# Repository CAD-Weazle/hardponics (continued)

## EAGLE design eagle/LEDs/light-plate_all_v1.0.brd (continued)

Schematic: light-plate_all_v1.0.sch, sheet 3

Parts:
C30D, C31D, C32D: 10U/50V; CAP0603
C30P, C31P, C32P: 1U; CAP0603
D30, D31, D32: MBR0530; DIODE_SOD123
H5, H6, H7, H8, H9, H10: HOLE_PTH_1.0MM
L30, L31, L32: SDR0604-101KL; L_SDR0604
LD30DR, LD30DR1, LD30DR2, LD30DR3, LD30DR4, LD30DR5, LD30DR6, LD30DR7, LD30DR8, LD30DR9, LD30DR10, LD30DR11, LD30DR12, LD30DR13, LD30DR14, LD30DR15, LD30DR16, LD30DR17, LD30DR18, LD30DR19, LD30DR20, LD30DR21, LD30DR22, LD30DR23, LD30DR24, LD30DR25, LD30DR26, LD30DR27, LD30DR28, LD30DR29, LD30DR30, LD30DR31, LD30DR32, LD30DR33, LD30DR34, LD30DR35, LD30DR36, LD30DR37, LD30DR38, LD30DR39, LD30DR40, LD30DR41, LD30DR42, LD30DR43, LD30DR44, LD30DR45, LD30DR46, LD30DR47, LD30DR48, LD30DR49, LD30DR50, LD30DR51, LD30DR52, LD30DR53, LD30DR54, LD30DR55, LD30DR56, LD30DR57, LD30DR58, LD30DR59, LD30DR60, LD30DR61, LD30DR62, LD30DR63, LD30DR64, LD30DR65, LD30DR66, LD30DR67, LD30DR68, LD30DR69, LD30DR70, LD30DR71, LD30DR72, LD30DR73, LD30DR74, LD30DR75, LD30DR76, LD30DR77, LD30DR78, LD30DR79, LD30DR80, LD30DR81, LD30DR82, LD30DR83, LD30DR84, LD30DR85, LD30DR86, LD30DR87, LD30DR88, LD30DR89, LD30DR90, LD30DR91, LD30DR92, LD30DR93, LD30DR94, LD30DR95, LD30DR96, LD30DR97, LD30DR98: L1SP-DRD00035R0000; LED_SMD_SUNPLUS35_REVERSED
R30, R31, R32: 0R5; RES0603
R30P, R31P, R32P: 10K; RES0603
U30, U31, U32: AL8860; SOT23-5

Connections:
DRED_PWM0: R30P.1; also elsewhere on the board
DRED_PWM1: R31P.1; also elsewhere on the board
DRED_PWM2: R32P.1; also elsewhere on the board
GND: C30D.2, C30P.2, C31D.2, C31P.2, C32D.2, C32P.2, U30.2 (2.GND), U31.2 (2.GND), U32.2 (2.GND); also elsewhere on the board
unnamed: C30P.1, R30P.2, U30.3 (3.VSET)
unnamed: LD30DR.A (-), LD30DR1.C (+)
unnamed: LD30DR1.A (-), LD30DR2.C (+)
unnamed: LD30DR2.A (-), LD30DR3.C (+)
unnamed: LD30DR3.A (-), LD30DR4.C (+)
unnamed: LD30DR4.A (-), LD30DR5.C (+)
unnamed: LD30DR5.A (-), LD30DR6.C (+)
unnamed: LD30DR6.A (-), LD30DR7.C (+)
unnamed: LD30DR7.A (-), LD30DR8.C (+)
unnamed: LD30DR8.A (-), LD30DR9.C (+)
unnamed: LD30DR9.A (-), LD30DR10.C (+)
unnamed: LD30DR11.A (-), LD30DR12.C (+)
unnamed: LD30DR12.A (-), LD30DR13.C (+)
unnamed: LD30DR13.A (-), LD30DR14.C (+)
unnamed: LD30DR14.A (-), LD30DR15.C (+)
unnamed: LD30DR15.A (-), LD30DR16.C (+)
unnamed: LD30DR16.A (-), LD30DR17.C (+)
unnamed: LD30DR17.A (-), LD30DR18.C (+)
unnamed: LD30DR18.A (-), LD30DR19.C (+)
unnamed: LD30DR19.A (-), LD30DR20.C (+)
unnamed: LD30DR20.A (-), LD30DR21.C (+)
unnamed: LD30DR22.A (-), LD30DR23.C (+)
unnamed: LD30DR23.A (-), LD30DR24.C (+)
unnamed: LD30DR24.A (-), LD30DR25.C (+)
unnamed: LD30DR25.A (-), LD30DR26.C (+)
unnamed: LD30DR26.A (-), LD30DR27.C (+)
unnamed: LD30DR27.A (-), LD30DR28.C (+)
unnamed: LD30DR28.A (-), LD30DR29.C (+)
unnamed: LD30DR29.A (-), LD30DR30.C (+)
unnamed: LD30DR30.A (-), LD30DR31.C (+)
unnamed: LD30DR31.A (-), LD30DR32.C (+)
unnamed: LD30DR33.A (-), LD30DR34.C (+)
unnamed: LD30DR34.A (-), LD30DR35.C (+)
unnamed: LD30DR35.A (-), LD30DR36.C (+)
unnamed: LD30DR36.A (-), LD30DR37.C (+)
unnamed: LD30DR37.A (-), LD30DR38.C (+)
unnamed: LD30DR38.A (-), LD30DR39.C (+)
unnamed: LD30DR39.A (-), LD30DR40.C (+)
unnamed: LD30DR40.A (-), LD30DR41.C (+)
unnamed: LD30DR41.A (-), LD30DR42.C (+)
unnamed: LD30DR42.A (-), LD30DR43.C (+)
unnamed: LD30DR44.A (-), LD30DR45.C (+)
unnamed: LD30DR45.A (-), LD30DR46.C (+)
unnamed: LD30DR46.A (-), LD30DR47.C (+)
unnamed: LD30DR47.A (-), LD30DR48.C (+)
unnamed: LD30DR48.A (-), LD30DR49.C (+)
unnamed: LD30DR49.A (-), LD30DR50.C (+)
unnamed: LD30DR50.A (-), LD30DR51.C (+)
unnamed: LD30DR51.A (-), LD30DR52.C (+)
unnamed: LD30DR52.A (-), LD30DR53.C (+)
unnamed: LD30DR53.A (-), LD30DR54.C (+)
unnamed: LD30DR55.A (-), LD30DR56.C (+)
unnamed: LD30DR56.A (-), LD30DR57.C (+)
unnamed: LD30DR57.A (-), LD30DR58.C (+)
unnamed: LD30DR58.A (-), LD30DR59.C (+)
unnamed: LD30DR59.A (-), LD30DR60.C (+)
unnamed: LD30DR60.A (-), LD30DR61.C (+)
unnamed: LD30DR61.A (-), LD30DR62.C (+)
unnamed: LD30DR62.A (-), LD30DR63.C (+)
unnamed: LD30DR63.A (-), LD30DR64.C (+)
unnamed: LD30DR64.A (-), LD30DR65.C (+)
unnamed: LD30DR66.A (-), LD30DR67.C (+)
unnamed: LD30DR67.A (-), LD30DR68.C (+)
unnamed: LD30DR68.A (-), LD30DR69.C (+)
unnamed: LD30DR69.A (-), LD30DR70.C (+)
unnamed: LD30DR70.A (-), LD30DR71.C (+)
unnamed: LD30DR71.A (-), LD30DR72.C (+)
unnamed: LD30DR72.A (-), LD30DR73.C (+)
unnamed: LD30DR73.A (-), LD30DR74.C (+)
unnamed: LD30DR74.A (-), LD30DR75.C (+)
unnamed: LD30DR75.A (-), LD30DR76.C (+)
unnamed: LD30DR77.A (-), LD30DR78.C (+)
unnamed: LD30DR78.A (-), LD30DR79.C (+)
unnamed: LD30DR79.A (-), LD30DR80.C (+)
unnamed: LD30DR80.A (-), LD30DR81.C (+)
unnamed: LD30DR81.A (-), LD30DR82.C (+)
unnamed: LD30DR82.A (-), LD30DR83.C (+)
unnamed: LD30DR83.A (-), LD30DR84.C (+)
unnamed: LD30DR84.A (-), LD30DR85.C (+)
unnamed: LD30DR85.A (-), LD30DR86.C (+)
unnamed: LD30DR86.A (-), LD30DR87.C (+)
unnamed: LD30DR88.A (-), LD30DR89.C (+)
unnamed: LD30DR89.A (-), LD30DR90.C (+)
unnamed: LD30DR90.A (-), LD30DR91.C (+)
unnamed: LD30DR91.A (-), LD30DR92.C (+)
unnamed: LD30DR92.A (-), LD30DR93.C (+)
unnamed: LD30DR93.A (-), LD30DR94.C (+)
unnamed: LD30DR94.A (-), LD30DR95.C (+)
unnamed: LD30DR95.A (-), LD30DR96.C (+)
unnamed: LD30DR96.A (-), LD30DR97.C (+)
unnamed: LD30DR97.A (-), LD30DR98.C (+)
unnamed: H5.1, L30.1, LD30DR10.A (-), LD30DR21.A (-), LD30DR32.A (-)
unnamed: H8.1, LD30DR33.C (+), LD30DR44.C (+), LD30DR55.C (+), R31.2, U31.4 (4.ISENSE)
unnamed: D30.2 (+), L30.2, U30.1 (1.LX)
unnamed: H6.1, LD30DR.C (+), LD30DR11.C (+), LD30DR22.C (+), R30.2, U30.4 (4.ISENSE)
unnamed: H7.1, L31.1, LD30DR43.A (-), LD30DR54.A (-), LD30DR65.A (-)
unnamed: H10.1, LD30DR66.C (+), LD30DR77.C (+), LD30DR88.C (+), R32.2, U32.4 (4.ISENSE)
unnamed: H9.1, L32.1, LD30DR76.A (-), LD30DR87.A (-), LD30DR98.A (-)
unnamed: D31.2 (+), L31.2, U31.1 (1.LX)
unnamed: C31P.1, R31P.2, U31.3 (3.VSET)
unnamed: D32.2 (+), L32.2, U32.1 (1.LX)
unnamed: C32P.1, R32P.2, U32.3 (3.VSET)
VDD_24V: C30D.1, C31D.1, C32D.1, D30.1- (-), D31.1- (-), D32.1- (-), R30.1, R31.1, R32.1, U30.5 (5.VIN), U31.5 (5.VIN), U32.5 (5.VIN); also elsewhere on the board

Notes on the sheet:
* PINNING
* FUNCTIONALITY
* PHYSICAL SIZE
* LAID OUT
* COMPS IN LIB
* IN HOUSE
: OK
Light Plate - Deep Red LEDs
1.0
180528

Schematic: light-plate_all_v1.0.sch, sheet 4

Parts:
C40D, C50D: 10U/50V; CAP0603
C40P, C50P: 1U; CAP0603
D40, D50: MBR0530; DIODE_SOD123
H11, H12, H13, H14, H15, H16: HOLE_PTH_1.0MM
L40, L50: SDR0604-101KL; L_SDR0604
LD5AFR, LD5AFR1, LD50FR, LD50FR1, LD51FR, LD51FR1, LD52FR, LD52FR1, LD53FR, LD53FR1, LD54FR, LD54FR1, LD55FR, LD55FR1, LD56FR, LD56FR1, LD57FR, LD57FR1, LD58FR, LD58FR1, LD59FR, LD59FR1: L1SP-DRD00035R0000; LED_SMD_SUNPLUS35_REVERSED
LD30B1, LD30B3, LD30B4, LD31B1, LD31B3, LD31B4, LD32B1, LD32B3, LD32B4, LD33B1, LD33B3, LD33B4, LD34B1, LD34B3, LD34B4, LD35B1, LD35B3, LD35B4, LD36B1, LD36B3, LD36B4, LD40B, LD41B, LD42B, LD43B, LD44B, LD45B, LD46B: L1SP-RYL0003500000; LED_SMD_SUNPLUS35
R40, R50: 0R5; RES0603
R40P, R50P: 10K; RES0603
U40, U50: AL8860; SOT23-5

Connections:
FRED_PWM0: R50P.1; also elsewhere on the board
GND: C40D.2, C40P.2, C50D.2, C50P.2, U40.2 (2.GND), U50.2 (2.GND); also elsewhere on the board
unnamed: LD30B1.C (-), LD31B1.A (+)
unnamed: LD31B1.C (-), LD32B1.A (+)
unnamed: LD32B1.C (-), LD33B1.A (+)
unnamed: LD33B1.C (-), LD34B1.A (+)
unnamed: LD34B1.C (-), LD35B1.A (+)
unnamed: LD35B1.C (-), LD36B1.A (+)
unnamed: LD30B4.C (-), LD31B4.A (+)
unnamed: LD31B4.C (-), LD32B4.A (+)
unnamed: LD32B4.C (-), LD33B4.A (+)
unnamed: LD33B4.C (-), LD34B4.A (+)
unnamed: LD34B4.C (-), LD35B4.A (+)
unnamed: LD35B4.C (-), LD36B4.A (+)
unnamed: LD40B.C (-), LD41B.A (+)
unnamed: LD41B.C (-), LD42B.A (+)
unnamed: LD42B.C (-), LD43B.A (+)
unnamed: LD43B.C (-), LD44B.A (+)
unnamed: LD44B.C (-), LD45B.A (+)
unnamed: LD45B.C (-), LD46B.A (+)
unnamed: LD30B3.C (-), LD31B3.A (+)
unnamed: LD31B3.C (-), LD32B3.A (+)
unnamed: LD32B3.C (-), LD33B3.A (+)
unnamed: LD33B3.C (-), LD34B3.A (+)
unnamed: LD34B3.C (-), LD35B3.A (+)
unnamed: LD35B3.C (-), LD36B3.A (+)
unnamed: LD50FR.A (-), LD51FR.C (+)
unnamed: LD51FR.A (-), LD52FR.C (+)
unnamed: LD52FR.A (-), LD53FR.C (+)
unnamed: LD53FR.A (-), LD54FR.C (+)
unnamed: LD54FR.A (-), LD55FR.C (+)
unnamed: LD55FR.A (-), LD56FR.C (+)
unnamed: LD56FR.A (-), LD57FR.C (+)
unnamed: LD57FR.A (-), LD58FR.C (+)
unnamed: LD58FR.A (-), LD59FR.C (+)
unnamed: LD5AFR.C (+), LD59FR.A (-)
unnamed: LD50FR1.A (-), LD51FR1.C (+)
unnamed: LD51FR1.A (-), LD52FR1.C (+)
unnamed: LD52FR1.A (-), LD53FR1.C (+)
unnamed: LD53FR1.A (-), LD54FR1.C (+)
unnamed: LD54FR1.A (-), LD55FR1.C (+)
unnamed: LD55FR1.A (-), LD56FR1.C (+)
unnamed: LD56FR1.A (-), LD57FR1.C (+)
unnamed: LD57FR1.A (-), LD58FR1.C (+)
unnamed: LD58FR1.A (-), LD59FR1.C (+)
unnamed: LD5AFR1.C (+), LD59FR1.A (-)
unnamed: H11.1, H15.1, L40.1, LD36B1.C (-), LD36B3.C (-), LD36B4.C (-), LD46B.C (-)
unnamed: H12.1, LD30B1.A (+), LD30B3.A (+), LD30B4.A (+), LD40B.A (+), R40.2, U40.4 (4.ISENSE)
unnamed: H14.1, H16.1, LD50FR.C (+), LD50FR1.C (+), R50.2, U50.4 (4.ISENSE)
unnamed: D50.2 (+), L50.2, U50.1 (1.LX)
unnamed: C50P.1, R50P.2, U50.3 (3.VSET)
unnamed: H13.1, L50.1, LD5AFR.A (-), LD5AFR1.A (-)
unnamed: D40.2 (+), L40.2, U40.1 (1.LX)
unnamed: C40P.1, R40P.2, U40.3 (3.VSET)
RBLU_PWM0: R40P.1; also elsewhere on the board
VDD_24V: C40D.1, C50D.1, D40.1- (-), D50.1- (-), R40.1, R50.1, U40.5 (5.VIN), U50.5 (5.VIN); also elsewhere on the board

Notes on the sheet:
* PINNING
* FUNCTIONALITY
* PHYSICAL SIZE
* LAID OUT
* COMPS IN LIB
* IN HOUSE
: OK
Light Plate - Royal Blue & Far Red LEDs
1.0
180528

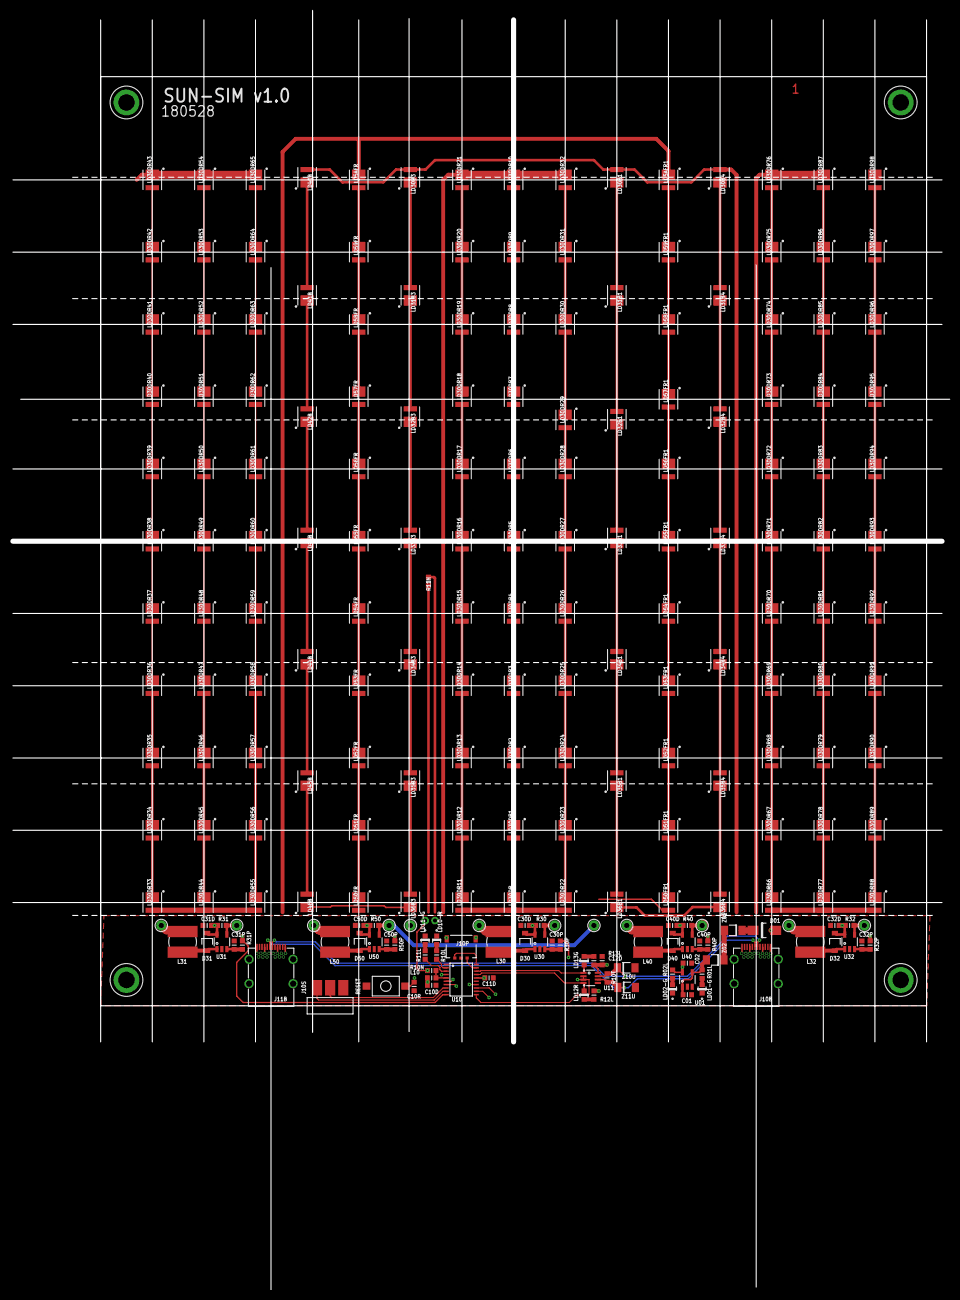
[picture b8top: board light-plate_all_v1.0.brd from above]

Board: 4 copper layers, 181.5 x 247.9 mm, 235 parts (0 on the bottom side), 185 nets.

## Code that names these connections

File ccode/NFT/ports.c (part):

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// GPIO Port A settings
static const struct port_info porta[16] = 
{
  [ 0] = {GPIO_MODE_AN,  GPIO_SPEED_FREQ_LOW,  GPIO_OTYPE_PP, GPIO_NOPULL},                  // PAR       - ADC[0]
  [ 1] = {GPIO_MODE_AN,  GPIO_SPEED_FREQ_LOW,  GPIO_OTYPE_PP, GPIO_NOPULL},                  // EC        - ADC[1]
  [ 2] = {GPIO_MODE_AF,  GPIO_SPEED_FREQ_HIGH, GPIO_OTYPE_PP, GPIO_NOPULL, GPIO_AF7_USART2}, // SER_TXD   - UART2   
  [ 3] = {GPIO_MODE_AF , GPIO_SPEED_FREQ_HIGH, GPIO_OTYPE_PP, GPIO_NOPULL, GPIO_AF7_USART2}, // SER_RXD   - UART2   
  [ 4] = {GPIO_MODE_AN,  GPIO_SPEED_FREQ_LOW,  GPIO_OTYPE_PP, GPIO_NOPULL},                  // EC_DAC    - DAC[1]
  [ 5] = {GPIO_MODE_AF,  GPIO_SPEED_FREQ_HIGH, GPIO_OTYPE_PP, GPIO_NOPULL, GPIO_AF5_SPI1},   // OLED_SCK  - SPI1
  [ 6] = {GPIO_MODE_AN,  GPIO_SPEED_FREQ_LOW,  GPIO_OTYPE_OD, GPIO_NOPULL},                  // EC_NTC    - ADC[6]
  [ 7] = {GPIO_MODE_AF,  GPIO_SPEED_FREQ_HIGH, GPIO_OTYPE_PP, GPIO_NOPULL, GPIO_AF5_SPI1},   // OLED_MOSI - SPI1
  [ 8] = {GPIO_MODE_OUT, GPIO_SPEED_FREQ_HIGH, GPIO_OTYPE_OD, GPIO_NOPULL},                  // SHT_DAT   - SHT15 data (OD)
//[ 8] = {GPIO_MODE_AF,  GPIO_SPEED_FREQ_HIGH, GPIO_OTYPE_PP, GPIO_NOPULL, GPIO_AF0_MCO},    // MCO       (dev only)
  [ 9] = {GPIO_MODE_OUT, GPIO_SPEED_FREQ_HIGH, GPIO_OTYPE_PP, GPIO_NOPULL},                  // SHT_CLK   - SHT15 clock (PP)
  [10] = {GPIO_MODE_OUT, GPIO_SPEED_FREQ_LOW,  GPIO_OTYPE_PP, GPIO_PULLUP},                  // SENSOR_PWR_L
  [11] = {GPIO_MODE_OUT, GPIO_SPEED_FREQ_LOW,  GPIO_OTYPE_PP, GPIO_PULLUP},                  // OLED_CS_L
  [12] = {GPIO_MODE_OUT, GPIO_SPEED_FREQ_LOW,  GPIO_OTYPE_PP, GPIO_PULLUP},                  // OLED_CD
  [13] = {GPIO_MODE_AF,  GPIO_SPEED_FREQ_HIGH, GPIO_OTYPE_PP, GPIO_PULLUP, GPIO_AF0_SWJ},    // SWD_IO    - prog port
  [14] = {GPIO_MODE_AF,  GPIO_SPEED_FREQ_HIGH, GPIO_OTYPE_PP, GPIO_PULLUP, GPIO_AF0_SWJ},    // SWD_CLK   - prog port
  [15] = {GPIO_MODE_OUT, GPIO_SPEED_FREQ_LOW,  GPIO_OTYPE_PP, GPIO_NOPULL},                  // REF_EC
};

// GPIO Port A settings - STOP mode
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  [10] = {GPIO_MODE_AN,  GPIO_SPEED_FREQ_LOW, GPIO_OTYPE_PP, GPIO_NOPULL},                   //
  [11] = {GPIO_MODE_AN,  GPIO_SPEED_FREQ_LOW, GPIO_OTYPE_PP, GPIO_PULLDOWN},                 //
  [12] = {GPIO_MODE_AN,  GPIO_SPEED_FREQ_LOW, GPIO_OTYPE_PP, GPIO_PULLDOWN},                 //
  [13] = {GPIO_MODE_IN,  GPIO_SPEED_FREQ_LOW, GPIO_OTYPE_PP, GPIO_PULLUP},                   // SWD_IO    - prog port
  [14] = {GPIO_MODE_IN,  GPIO_SPEED_FREQ_LOW, GPIO_OTYPE_PP, GPIO_PULLUP},                   // SWD_CLK   - prog port
  [15] = {GPIO_MODE_AN,  GPIO_SPEED_FREQ_LOW, GPIO_OTYPE_PP, GPIO_PULLDOWN},                 // 
};

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static const struct port_info portb[16] = 
{
  [ 0] = {GPIO_MODE_AN,  GPIO_SPEED_FREQ_LOW,  GPIO_OTYPE_PP, GPIO_NOPULL},                  // VBAT      - ADC8 
  [ 1] = {GPIO_MODE_AN,  GPIO_SPEED_FREQ_LOW,  GPIO_OTYPE_PP, GPIO_NOPULL},                  // IBAT      - ADC9
  [ 2] = {GPIO_MODE_OUT, GPIO_SPEED_FREQ_LOW,  GPIO_OTYPE_PP, GPIO_PULLDOWN},                // VGND
  [ 3] = {GPIO_MODE_OUT, GPIO_SPEED_FREQ_LOW,  GPIO_OTYPE_PP, GPIO_PULLDOWN},                // PUMP1
  [ 4] = {GPIO_MODE_IN,  GPIO_SPEED_FREQ_HIGH, GPIO_OTYPE_PP, GPIO_NOPULL},                  // SAMPLE1
  [ 5] = {GPIO_MODE_IN,  GPIO_SPEED_FREQ_HIGH, GPIO_OTYPE_PP, GPIO_NOPULL},                  // BUTTON0
  [ 6] = {GPIO_MODE_IN,  GPIO_SPEED_FREQ_HIGH, GPIO_OTYPE_PP, GPIO_NOPULL},                  // BUTTON1
  [ 7] = {GPIO_MODE_IN,  GPIO_SPEED_FREQ_HIGH, GPIO_OTYPE_PP, GPIO_NOPULL},                  // BUTTON2
  [ 8] = {GPIO_MODE_OUT, GPIO_SPEED_FREQ_LOW,  GPIO_OTYPE_PP, GPIO_PULLDOWN},                // PUMP0
  [ 9] = {GPIO_MODE_IN,  GPIO_SPEED_FREQ_HIGH, GPIO_OTYPE_OD, GPIO_PULLUP},                  // <> fix this
  [10] = {GPIO_MODE_AF,  GPIO_SPEED_FREQ_LOW,  GPIO_OTYPE_PP, GPIO_NOPULL, GPIO_AF7_USART3}, // WIFI_TXD  - UART3
  [11] = {GPIO_MODE_AF,  GPIO_SPEED_FREQ_LOW,  GPIO_OTYPE_PP, GPIO_NOPULL, GPIO_AF7_USART3}, // WIFI_RXD  - UART3
  [12] = {GPIO_MODE_IN,  GPIO_SPEED_FREQ_HIGH, GPIO_OTYPE_PP, GPIO_NOPULL},                  // SAMPLE2
  [13] = {GPIO_MODE_IN,  GPIO_SPEED_FREQ_HIGH, GPIO_OTYPE_PP, GPIO_NOPULL},                  // BUTTON3
  [14] = {GPIO_MODE_AN,  GPIO_SPEED_FREQ_LOW,  GPIO_OTYPE_PP, GPIO_NOPULL},                  // VSOL      - ADC20
  [15] = {GPIO_MODE_AF,  GPIO_SPEED_FREQ_HIGH, GPIO_OTYPE_PP, GPIO_NOPULL, GPIO_AF5_SPI2},   // LED_DIN   - MOSI2
};

// GPIO Port B settings - STOP mode
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// GPIO Port C settings
static const struct port_info portc[16] = 
{
  [13] = {GPIO_MODE_IN,  GPIO_SPEED_FREQ_LOW,  GPIO_OTYPE_PP, GPIO_NOPULL},                  // SPEED0 <> now IBAT sign
  [14] = {GPIO_MODE_IN,  GPIO_SPEED_FREQ_LOW,  GPIO_OTYPE_PP, GPIO_NOPULL},                  // SPEED1
  [15] = {GPIO_MODE_OUT, GPIO_SPEED_FREQ_LOW,  GPIO_OTYPE_OD, GPIO_PULLUP},                  // WIFI_EN
};

// GPIO Port C settings - STOP mode
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// GPIO Port H settings
static const struct port_info porth[16] = 
{
  [ 0] = {GPIO_MODE_OUT, GPIO_SPEED_FREQ_LOW,  GPIO_OTYPE_PP, GPIO_PULLDOWN},                // LED_RED
  [ 1] = {GPIO_MODE_OUT, GPIO_SPEED_FREQ_LOW,  GPIO_OTYPE_PP, GPIO_PULLDOWN},                // LED_GRN
};

// GPIO Port H settings - STOP mode
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  gnd_disconnect ();

  // ESP32 active
  gpio_set (GPIOC, WIFI_EN);
}

// set GPIO to low power inputs in STOP mode
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// red LED routines
void led_red_on (void)
{
  gpio_set (GPIOH, LED_RED);
}

void led_red_off (void)
{
  gpio_clr (GPIOH, LED_RED);
}

void led_red_toggle (void)
{
  if (GPIOH->ODR & (1 << LED_RED))
    gpio_clr (GPIOH, LED_RED);
  else
    gpio_set (GPIOH, LED_RED);
}

void led_red_flash (uint16_t delay)
{
  gpio_set (GPIOH, LED_RED);
  msleep (delay);
  gpio_clr (GPIOH, LED_RED);
}

void led_grn_on (void)
{
  gpio_set (GPIOH, LED_GRN);
}

void led_grn_off (void)
{
  gpio_clr (GPIOH, LED_GRN);
}

void led_grn_toggle (void)
{
  if (GPIOH->ODR & (1 << LED_GRN))
    gpio_clr (GPIOH, LED_GRN);
  else
    gpio_set (GPIOH, LED_GRN);
}

void led_grn_flash (uint16_t delay)
{
  gpio_set (GPIOH, LED_GRN);
  msleep (delay);
  gpio_clr (GPIOH, LED_GRN);
}

// apply power to SHT15 sensor
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// apply power to EC circuit
void ec_power_on (void)
{
  gpio_set (GPIOA, REF_EC);
}

// remove power from EC circuit
void ec_power_off (void)
{
  gpio_clr (GPIOA, REF_EC);
}

// water pump control
void pump0_on (void)
{
  gpio_set (GPIOB, PUMP0);
}

void pump0_off (void)
{
  gpio_clr (GPIOB, PUMP0);
}

void pump1_on (void)
{
  gpio_set (GPIOB, PUMP1);
}

void pump1_off (void)
{
  gpio_clr (GPIOB, PUMP1);
}

// VSOL/VACCU voltage dividers 
void gnd_connect (void)
{
  gpio_clr (GPIOB, VGND);
}

void gnd_disconnect (void)
{
  gpio_set (GPIOB, VGND);
}

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
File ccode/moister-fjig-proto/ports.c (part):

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{
  [ 0] = {GPIO_MODE_IN,  GPIO_SPEED_FREQ_HIGH, GPIO_OTYPE_PP, GPIO_NOPULL},                  // MOISTER: Cs - sample capacitor
  [ 1] = {GPIO_MODE_IN,  GPIO_SPEED_FREQ_HIGH, GPIO_OTYPE_PP, GPIO_NOPULL},                  // MOISTER: Ct - touch capacitor
  [ 2] = {GPIO_MODE_AF,  GPIO_SPEED_FREQ_HIGH, GPIO_OTYPE_PP, GPIO_PULLUP, GPIO_AF7_USART2}, // SER_TXD
  [ 3] = {GPIO_MODE_AF , GPIO_SPEED_FREQ_HIGH, GPIO_OTYPE_PP, GPIO_PULLUP, GPIO_AF7_USART2}, // SER_RXD
  [ 4] = {GPIO_MODE_AN,  GPIO_SPEED_FREQ_LOW,  GPIO_OTYPE_PP, GPIO_NOPULL},                  // LIGHT_OUT  - ADC[4]
  [ 5] = {GPIO_MODE_IN,  GPIO_SPEED_FREQ_LOW,  GPIO_OTYPE_PP, GPIO_PULLDOWN},                // NU
  [ 6] = {GPIO_MODE_IN,  GPIO_SPEED_FREQ_LOW,  GPIO_OTYPE_PP, GPIO_PULLDOWN},                // NU
  [ 7] = {GPIO_MODE_IN,  GPIO_SPEED_FREQ_LOW,  GPIO_OTYPE_PP, GPIO_PULLDOWN},                // NU
  [ 8] = {GPIO_MODE_AF,  GPIO_SPEED_FREQ_HIGH, GPIO_OTYPE_PP, GPIO_NOPULL, GPIO_AF0_MCO},    // CLOCK_OUT  - MCO (select FREQ_HIGH!!!1!)
  [ 9] = {GPIO_MODE_OUT, GPIO_SPEED_FREQ_LOW,  GPIO_OTYPE_PP, GPIO_NOPULL},                  // LED_RED
  [10] = {GPIO_MODE_OUT, GPIO_SPEED_FREQ_LOW,  GPIO_OTYPE_PP, GPIO_NOPULL},                  // LED_GRN
  [11] = {GPIO_MODE_OUT, GPIO_SPEED_FREQ_LOW,  GPIO_OTYPE_OD, GPIO_NOPULL},                  // VGND (open drain)
  [12] = {GPIO_MODE_IN,  GPIO_SPEED_FREQ_LOW,  GPIO_OTYPE_PP, GPIO_PULLDOWN},                // NU
  [13] = {GPIO_MODE_AF,  GPIO_SPEED_FREQ_HIGH, GPIO_OTYPE_PP, GPIO_NOPULL, GPIO_AF0_SWJ},    // SWD_IO
  [14] = {GPIO_MODE_AF,  GPIO_SPEED_FREQ_HIGH, GPIO_OTYPE_PP, GPIO_NOPULL, GPIO_AF0_SWJ},    // SWD_CLK 
  [15] = {GPIO_MODE_OUT, GPIO_SPEED_FREQ_LOW,  GPIO_OTYPE_PP, GPIO_NOPULL},                  // BAT_SINK
};

// GPIO Port A settings - STOP mode
static const struct port_info stopa[16] = 
{
  [ 0] = {GPIO_MODE_IN,  GPIO_SPEED_FREQ_LOW, GPIO_OTYPE_PP, GPIO_PULLUP},                   // BLE_TXI_L  - keep input for EXTI event 
  [ 1] = {GPIO_MODE_AN,  GPIO_SPEED_FREQ_LOW, GPIO_OTYPE_PP, GPIO_PULLDOWN},                 // BLE_CUR    - ADC[1]
  [ 2] = {GPIO_MODE_AF,  GPIO_SPEED_FREQ_LOW, GPIO_OTYPE_PP, GPIO_PULLUP,  GPIO_AF7_USART2}, // SER_TXD    - don't change function, keep TxD high
  [ 3] = {GPIO_MODE_AN,  GPIO_SPEED_FREQ_LOW, GPIO_OTYPE_PP, GPIO_PULLUP},                   // SER_RXD
  [ 4] = {GPIO_MODE_AN,  GPIO_SPEED_FREQ_LOW, GPIO_OTYPE_PP, GPIO_PULLDOWN},                 // 
  [ 5] = {GPIO_MODE_AN,  GPIO_SPEED_FREQ_LOW, GPIO_OTYPE_PP, GPIO_PULLDOWN},                 // 
  [ 6] = {GPIO_MODE_AN,  GPIO_SPEED_FREQ_LOW, GPIO_OTYPE_PP, GPIO_PULLDOWN},                 // 
  [ 7] = {GPIO_MODE_AN,  GPIO_SPEED_FREQ_LOW, GPIO_OTYPE_PP, GPIO_PULLDOWN},                 // 
  [ 8] = {GPIO_MODE_AN,  GPIO_SPEED_FREQ_LOW, GPIO_OTYPE_PP, GPIO_PULLDOWN},                 // 
  [ 9] = {GPIO_MODE_AN,  GPIO_SPEED_FREQ_LOW, GPIO_OTYPE_PP, GPIO_PULLDOWN},                 // 
  [10] = {GPIO_MODE_AN,  GPIO_SPEED_FREQ_LOW, GPIO_OTYPE_PP, GPIO_NOPULL},                   // VGND         - open drain
  [11] = {GPIO_MODE_AN,  GPIO_SPEED_FREQ_LOW, GPIO_OTYPE_PP, GPIO_PULLDOWN},                 // 
  [12] = {GPIO_MODE_AN,  GPIO_SPEED_FREQ_LOW, GPIO_OTYPE_PP, GPIO_PULLDOWN},                 // 
  [13] = {GPIO_MODE_IN,  GPIO_SPEED_FREQ_LOW, GPIO_OTYPE_PP, GPIO_PULLDOWN},                 // SWD_IO
  [14] = {GPIO_MODE_IN,  GPIO_SPEED_FREQ_LOW, GPIO_OTYPE_PP, GPIO_PULLDOWN},                 // SWD_CLK
  [15] = {GPIO_MODE_AN,  GPIO_SPEED_FREQ_LOW, GPIO_OTYPE_PP, GPIO_PULLDOWN},                 // 
};

// GPIO Port B settings
static const struct port_info portb[16] = 
{
  [ 0] = {GPIO_MODE_IN,  GPIO_SPEED_FREQ_LOW,  GPIO_OTYPE_PP, GPIO_PULLUP},                  // BLE_MODE
  [ 1] = {GPIO_MODE_OUT, GPIO_SPEED_FREQ_LOW,  GPIO_OTYPE_PP, GPIO_PULLUP},                  // BLE_RESET_L
  [ 2] = {GPIO_MODE_IN,  GPIO_SPEED_FREQ_LOW,  GPIO_OTYPE_PP, GPIO_PULLDOWN},                // NU
  [ 3] = {GPIO_MODE_AN,  GPIO_SPEED_FREQ_LOW,  GPIO_OTYPE_PP, GPIO_NOPULL},                  // CAP-METER: COMP-
  [ 4] = {GPIO_MODE_IN,  GPIO_SPEED_FREQ_LOW,  GPIO_OTYPE_PP, GPIO_PULLDOWN},                // NU
  [ 5] = {GPIO_MODE_AN,  GPIO_SPEED_FREQ_LOW,  GPIO_OTYPE_PP, GPIO_NOPULL},                  // CAP-METER: COMP+
  [ 6] = {GPIO_MODE_IN,  GPIO_SPEED_FREQ_LOW,  GPIO_OTYPE_PP, GPIO_PULLDOWN},                // NU
  [ 7] = {GPIO_MODE_OUT, GPIO_SPEED_FREQ_LOW,  GPIO_OTYPE_OD, GPIO_NOPULL},                  // SHT_DAT - CAP-METER TEST: R_DISCHARGE
  [ 8] = {GPIO_MODE_OUT, GPIO_SPEED_FREQ_LOW,  GPIO_OTYPE_PP, GPIO_NOPULL},                  // SHT_CLK - CAP-METER TEST: R_CHARGE
  [ 9] = {GPIO_MODE_OUT, GPIO_SPEED_FREQ_LOW,  GPIO_OTYPE_PP, GPIO_NOPULL},                  // SENSOR_PWR_L
  [10] = {GPIO_MODE_AF,  GPIO_SPEED_FREQ_LOW,  GPIO_OTYPE_PP, GPIO_NOPULL, GPIO_AF7_USART3}, // BLE_RXD      - UART3
  [11] = {GPIO_MODE_AF,  GPIO_SPEED_FREQ_LOW,  GPIO_OTYPE_PP, GPIO_NOPULL, GPIO_AF7_USART3}, // BLE_TXD      - UART3
  [12] = {GPIO_MODE_OUT, GPIO_SPEED_FREQ_LOW,  GPIO_OTYPE_PP, GPIO_NOPULL},                  // BLE_RXI_L
  [13] = {GPIO_MODE_AN,  GPIO_SPEED_FREQ_LOW,  GPIO_OTYPE_PP, GPIO_NOPULL},                  // VBAT
  [14] = {GPIO_MODE_AN,  GPIO_SPEED_FREQ_LOW,  GPIO_OTYPE_PP, GPIO_NOPULL},                  // VSYS
  [15] = {GPIO_MODE_IN,  GPIO_SPEED_FREQ_LOW,  GPIO_OTYPE_PP, GPIO_PULLDOWN},                // NU
};

// GPIO Port B settings - STOP mode
static const struct port_info stopb[16] = 
{
   [0] = {GPIO_MODE_AN,  GPIO_SPEED_FREQ_LOW,  GPIO_OTYPE_PP, GPIO_PULLUP},                  // BLE_MODE     - keep high
   [1] = {GPIO_MODE_AN,  GPIO_SPEED_FREQ_LOW,  GPIO_OTYPE_PP, GPIO_PULLUP},                  // BLE_RESET_L  - keep high
   [2] = {GPIO_MODE_AN,  GPIO_SPEED_FREQ_LOW,  GPIO_OTYPE_PP, GPIO_PULLDOWN},                // 
   [3] = {GPIO_MODE_AN,  GPIO_SPEED_FREQ_LOW,  GPIO_OTYPE_PP, GPIO_PULLDOWN},                // 
   [4] = {GPIO_MODE_AN,  GPIO_SPEED_FREQ_LOW,  GPIO_OTYPE_PP, GPIO_PULLDOWN},                // 
   [5] = {GPIO_MODE_AN,  GPIO_SPEED_FREQ_LOW,  GPIO_OTYPE_PP, GPIO_PULLDOWN},                // 
   [6] = {GPIO_MODE_AN,  GPIO_SPEED_FREQ_LOW,  GPIO_OTYPE_PP, GPIO_PULLDOWN},                // 
   [7] = {GPIO_MODE_AN,  GPIO_SPEED_FREQ_LOW,  GPIO_OTYPE_PP, GPIO_PULLDOWN},                // SHT_DAT 
   [8] = {GPIO_MODE_AN,  GPIO_SPEED_FREQ_LOW,  GPIO_OTYPE_PP, GPIO_PULLDOWN},                // SHT_CLK
   [9] = {GPIO_MODE_AN,  GPIO_SPEED_FREQ_LOW,  GPIO_OTYPE_PP, GPIO_PULLDOWN},                // 
  [10] = {GPIO_MODE_AN,  GPIO_SPEED_FREQ_LOW,  GPIO_OTYPE_PP, GPIO_NOPULL},                  // BLE_RXD      - UART3
  [11] = {GPIO_MODE_AN,  GPIO_SPEED_FREQ_LOW,  GPIO_OTYPE_PP, GPIO_NOPULL},                  // BLE_TXD      - UART3
  [12] = {GPIO_MODE_AN,  GPIO_SPEED_FREQ_LOW,  GPIO_OTYPE_PP, GPIO_PULLDOWN},                // 
  [13] = {GPIO_MODE_AN,  GPIO_SPEED_FREQ_LOW,  GPIO_OTYPE_PP, GPIO_NOPULL},                  // VBAT
  [14] = {GPIO_MODE_AN,  GPIO_SPEED_FREQ_LOW,  GPIO_OTYPE_PP, GPIO_NOPULL},                  // VSYS
  [15] = {GPIO_MODE_AN,  GPIO_SPEED_FREQ_LOW,  GPIO_OTYPE_PP, GPIO_PULLDOWN},                // 
};

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// red LED routines
void led_red_on (void)
{
  gpio_set (GPIOA, LED_RED);
}

void led_red_off (void)
{
  gpio_clr (GPIOA, LED_RED);
}

void led_red_toggle (void)
{
  if (GPIOA->ODR & (1 << LED_RED))
    gpio_clr (GPIOA, LED_RED);
  else
    gpio_set (GPIOA, LED_RED);
}

void led_red_flash (uint16_t delay)
{
  gpio_set (GPIOA, LED_RED);
  msleep (delay);
  gpio_clr (GPIOA, LED_RED);
}

// green LED routines
void led_grn_on (void)
{
  gpio_set (GPIOA, LED_GRN);
}

void led_grn_off (void)
{
  gpio_clr (GPIOA, LED_GRN);
}

void led_grn_toggle (void)
{
  if (GPIOA->ODR & (1 << LED_GRN))
    gpio_clr (GPIOA, LED_GRN);
  else
    gpio_set (GPIOA, LED_GRN);
}

void led_grn_flash (uint16_t delay)
{
  gpio_set (GPIOA, LED_GRN);
  msleep (delay);
  gpio_clr (GPIOA, LED_GRN);
}

// ** CAP-METER TEST
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// charge capacitor
void cap_charge (void)
{
  // PB6 to output, PB7 to input
  int tmp = GPIOB->MODER;

  tmp &= ~(0b11 << 2*SHT_DAT);
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  TIM5->CR1 |= TIM_CR1_CEN;

  // apply voltage to capacitor
  gpio_set (GPIOB, SHT_CLK);
}

// discharge capacitor
void cap_discharge (void)
{
  // PB6 to input, PB7 to output
  int tmp = GPIOB->MODER;

  tmp &= ~(0b11 << 2*SHT_DAT);
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  GPIOB->MODER = tmp;
  
  // drain charge to GND
  gpio_clr (GPIOB, SHT_DAT);
}


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
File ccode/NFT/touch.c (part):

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// date    : 220304
// last    : 230202
//
// note    : sampling capacitor on PB4  - group 6-1 
//           BUTTON0  capacitor on PB5  - group 6-2
//           BUTTON1  capacitor on PB6  - group 6-3
//           BUTTON2  capacitor on PB7  - group 6-4
//           
// note    : sampling capacitor on PB12 - group 7-1 
//           BUTTON3  capacitor on PB13 - group 7-2
//
// note    : charge transfer sequence:
// 
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  // enable Comparator interface clock to access RI registers
  RCC->APB1ENR |= RCC_APB1ENR_COMPEN;

  // no hysteresis on sampling cap pin PB4/PB12 (& PB5, PB6, PB7, PB13???)
  RI->HYSCR1 = (1 << (GPIO_CAP_SAMPLE1 + 16))    // add 16 for hi-word bits
             | (1 << (GPIO_CAP_BUTTON0 + 16))
             | (1 << (GPIO_CAP_BUTTON1 + 16))
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    // select sampling cap SAMPLE1 & BUTTON0
    case 0:
    {
      RI->ASCR2 = (1 << 4) | (1 <<  5);     // switches closed - PB4/PB5 (GRP6-1/GR6-2)
      break;
    }

    // select sampling cap SAMPLE1 & BUTTON1
    case 1:
    {
      RI->ASCR2 = (1 << 4) | (1 << 27);     // switches closed - PB4/PB6 (GRP6-1/GR6-3)
      break;
    }

    // select sampling cap SAMPLE1 & BUTTON2
    case 2:
    {
      RI->ASCR2 = (1 << 4) | (1 << 28);     // switches closed - PB4/PB7 (GRP6-1/GR6-4)
      break;
    }

    // select sampling cap SAMPLE2 & BUTTON3
    case 3:
    {
      RI->ASCR1 = (1 << 18) | (1 << 19);    // switches closed - PB12/PB13 (GRP7-1/GR7-2)
      break;
    }

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
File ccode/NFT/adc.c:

// file    : adc.c
// author  : rb
// purpose : STM32L1xx ARM ADC routines
// date    : 171130
// last    : 230315
//
// note    : VREFINT_CAL Raw data acquired at temperature of 30 °C ±5 °C VDDA= 3V ±10 mV x1FF800F8 - 0x1FF800F9
//           is used for ADC-to-voltage calculation

#include "includes.h"

// globals
float Vrefint = 1511.0;      // default Vrefint [ADC counts]

// data ADC channels
int ntc_raw;
int vbat_raw;
int vsol_raw;

int par_raw;
int par_old = 0;             // filter state
int par_avg;                 // ADC averaged data

int ibat_raw;
int ibat_old = 0;            // filter state
int ibat_avg;                // ADC averaged data

// init ADC1
void init_adc (void) 
{ 
  // enable clock for ADC1
  RCC->APB2ENR |= RCC_APB2ENR_ADC1EN;

  // set HSI divider 
  ADC->CCR = (0b00 << ADC_CCR_ADCPRE_Pos);       // ADC clock = HSI/1 (16/1 = 16Mc)

  // first get Vrefint before setting up scan sequence & stuff (used for ADC-to-voltage calculations)
  Vrefint = adc_read_vref ();

  // set ADC sample time
  // * channel sample times:
  // 0b000 =   3 cycles
  // 0b001 =  15 cycles
  // 0b010 =  28 cycles
  // 0b011 =  56 cycles
  // 0b100 =  84 cycles
  // 0b101 = 112 cycles
  // 0b110 = 144 cycles
  // 0b111 = 480 cycles
  ADC1->SMPR1 = (0b110 <<  0) |  // channel 20 -- VSOL (PB14)
                (0b110 <<  3) |  // channel 21
                (0b010 <<  6) |  // channel 22
                (0b010 <<  9) |  // channel 23
                (0b010 << 12) |  // channel 24
                (0b010 << 15) |  // channel 25
                (0b010 << 18) |  // channel 26
                (0b010 << 21) |  // channel 27
                (0b010 << 24) |  // channel 28
                (0b010 << 27);   // channel 29

  ADC1->SMPR2 = (0b010 <<  0) |  // channel 10
                (0b010 <<  3) |  // channel 11
                (0b010 <<  6) |  // channel 12
                (0b010 <<  9) |  // channel 13
                (0b010 << 12) |  // channel 14
                (0b010 << 15) |  // channel 15
                (0b010 << 18) |  // channel 16
                (0b110 << 21) |  // channel 17 -- Vrefint 
                (0b010 << 24) |  // channel 18 
                (0b010 << 27);   // channel 19 

  ADC1->SMPR3 = (0b110 <<  0) |  // channel 0  -- PAR  (PA0)
                (0b110 <<  3) |  // channel 1  -- EC   (PA1)
                (0b010 <<  6) |  // channel 2
                (0b010 <<  9) |  // channel 3
                (0b010 << 12) |  // channel 4
                (0b010 << 15) |  // channel 5
                (0b010 << 18) |  // channel 6  -- NTC  (PA6)
                (0b010 << 21) |  // channel 7
                (0b010 << 24) |  // channel 8  -- VBAT (PB0)
                (0b010 << 27);   // channel 9  -- IBAT (PB1) - noisy AF

  // setup scan sequence length & scan order regular channels 
  ADC1->SQR1 = (0 << ADC_SQR1_L_Pos);            // sequence length
  ADC1->SQR2 = 0;                                          
  ADC1->SQR3 = 0;                                          
  ADC1->SQR4 = 0;                                          
  ADC1->SQR5 = ADC_CHAN_VREF;
  
  // set EOC flag behavior
  ADC1->CR2 |= ADC_CR2_EOCS;                     // set EOC flag after every conversion

  // get Vrefint
  Vrefint = adc_read_vref ();
}

// read ADC channel
uint32_t adc_read_channel (uint8_t chan)
{
  // sequence length 
  ADC1->SQR1 = (0 << 20);                        // read single channel

  // set single ADC channel sequence
  ADC1->SQR5 = (chan << 0);   

  // enable ADC
  ADC1->CR2 |= ADC_CR2_ADON;

  // wait for ADC ready & Regular Channel ready  <> add this to older 'adc.c' source
  while (((ADC1->SR & ADC_SR_ADONS) == 0) || ((ADC1->SR & ADC_SR_RCNR) != 0))
    ;  

  // start conversion Regular Channel
  ADC1->CR2 |= ADC_CR2_SWSTART;

  // wait for conversion ready, check EOC flag (called EOCS for some reason, WTF?)
  // note: hangs with leaving stop mode (fix this)
  while ((ADC1->SR & ADC_SR_EOCS) == 0)
    ;  

  // disable ADC to save power
  ADC1->CR2 &= ~ADC_CR2_ADON;

  // read result
  return (ADC1->DR);
}

// read internal reference voltage VREFINT
float adc_read_vref (void)
{
  uint32_t dat = 0;

  // sample VREFINT a few times
  for (int i = 0; i < ADC_NUM_REFSAMPLES; i++)
  {
    dat += adc_read_channel (ADC_CHAN_VREF);
  }

  // return average
  return ((float)dat / ADC_NUM_REFSAMPLES);
}

// read all ADC channels & filter if needed
void adc_update (void)
{
  static int cnt = 0;
  static int first = 1;

  // no noise filter needed, read once per second
  if ((cnt++ >= 100) || (first == 1))
  {
    // connect voltage dividers to GND (VSOL/VACCU)
    gnd_connect ();
    msleep (20);  // relax a vit, let analog signals settle

//  par_raw  = adc_read_channel (ADC_CHAN_PAR);   // PAR light sensor
    ntc_raw  = adc_read_channel (ADC_CHAN_NTC);   // NTC sensor for EC sensor
    vbat_raw = adc_read_channel (ADC_CHAN_VBAT);  // battery voltage
    vsol_raw = adc_read_channel (ADC_CHAN_VSOL);  // solar panel voltage

    // disconnect voltage dividers from GND (VSOL/VACCU)
    gnd_disconnect ();

    cnt = 0;
  }

  // read battery current sensor sign bit first
  int sign;

  if (GPIOC->IDR & (1 << IBAT_SIGN))
    sign = 1; // postive: battery is charging
  else
    sign = -1;// negative: battery is discharging

  // IBAT noisy AF, filter needed
  ibat_raw = sign * adc_read_channel (ADC_CHAN_IBAT);

  // PAR noisy, needs filter?
  par_raw  = adc_read_channel (ADC_CHAN_PAR);   // PAR light sensor

  // speed up filter 
  if (first)
  {
    par_old = par_raw;
    ibat_old = ibat_raw;
    first = 0;
  }

  // exponential filter: Xn = (1-a).Xn-1 + a.New (a = 1/ADC_EXP_DEPTH) 
  par_avg = ((ADC_EXP_DEPTH_PAR-1)*par_old + par_raw)/ADC_EXP_DEPTH_PAR;

  // exponential filter: Xn = (1-a).Xn-1 + a.New (a = 1/ADC_EXP_DEPTH) 
  ibat_avg = ((ADC_EXP_DEPTH-1)*ibat_old + ibat_raw)/ADC_EXP_DEPTH;

  // update state
  par_old = par_avg;   
  ibat_old = ibat_avg;   
}

// read battery voltage 
float adc_read_vbat (void)
{
  // voltage divider, multiply result by factor
  return (4.0 * (VREFINT_VDDA*VREFINT_CAL_DAT * vbat_raw) / (Vrefint*ADC_FULLRANGE));
}

// read battery current
float adc_read_ibat (void)
{
  return (1000 * (VREFINT_VDDA*VREFINT_CAL_DAT*ibat_avg) / (Vrefint*ADC_FULLRANGE));
}

// read solar panel voltage
float adc_read_vsol (void)
{
  // voltage divider, multiply result by factor
  return (10.0908 * (VREFINT_VDDA*VREFINT_CAL_DAT * vsol_raw) / (Vrefint*ADC_FULLRANGE));
}

// read ADC channel PAR sensor
uint16_t adc_read_par (void)
{
//return (par_raw * PAR_LSB);
  return (par_avg * PAR_LSB);
}

// read ADC channel NTC of EC sensor
uint16_t adc_read_ntc (void)
{
  return (ntc_raw);
}

// dump ADC registers -- dev only
void adc_dump_registers (void)
{
  printf2 ("-- ADC registers --\n");
  printf2 ("ADC1_SR    : %08lx\n", ADC1->SR);
  printf2 ("ADC1_CR1   : %08lx\n", ADC1->CR1);
  printf2 ("ADC1_CR2   : %08lx\n", ADC1->CR2);
  printf2 ("ADC1_SMPR1 : %08lx\n", ADC1->SMPR1);
  printf2 ("ADC1_SMPR2 : %08lx\n", ADC1->SMPR2);
  printf2 ("ADC1_SMPR3 : %08lx\n", ADC1->SMPR3);
  printf2 ("ADC1_SQR1  : %08lx\n", ADC1->SQR1);
  printf2 ("ADC1_SQR2  : %08lx\n", ADC1->SQR2);
  printf2 ("ADC1_SQR3  : %08lx\n", ADC1->SQR3);
  printf2 ("ADC1_SQR4  : %08lx\n", ADC1->SQR4);
  printf2 ("ADC1_SQR5  : %08lx\n", ADC1->SQR5);
  printf2 ("ADC1_DR    : %08lx\n", ADC1->DR);
}

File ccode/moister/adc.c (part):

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  // 0b101 =  96 cycles
  // 0b110 = 192 cycles
  // 0b111 = 384 cycles
  ADC1->SMPR1 = (0b111 <<  0) |  // channel 20 -- Vsolar (PB14)
                (0b010 <<  3) |  // channel 21
                (0b010 <<  6) |  // channel 22
                (0b010 <<  9) |  // channel 23
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                (0b010 << 18) |  // channel 16
                (0b111 << 21) |  // channel 17 -- Vrefint 
                (0b010 << 24) |  // channel 18 
                (0b111 << 27);   // channel 19 -- Vbat (PB13)

  ADC1->SMPR3 = (0b010 << 27)    // channel 9
              | (0b010 << 24)    // channel 8
              | (0b011 << 21)    // channel 7  -- NTC3 (PA7)
              | (0b011 << 18)    // channel 6  -- NTC2 (PA6)
              | (0b011 << 15)    // channel 5  -- NTC1 (PA5)
              | (0b011 << 12)    // channel 4  -- NTC0 (PA4)
              | (0b010 <<  9)    // channel 3
              | (0b010 <<  6)    // channel 2
              | (0b010 <<  3)    // channel 1
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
